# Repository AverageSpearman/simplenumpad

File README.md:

# simplenumpad
A very basic, hacked together mechanical numpad.

## Introduction

This was made with the goal of having a numpad to go with a mechanical keyboard lacking one.
Since I didn't want to bother with either buying a kit or going to a manufacturer to get a pcb, this is made using basically as few new parts as possible.
Most of the parts that aren't the electronics are just random garbage around the house.

## Parts List
Because this project doesn't use a PCB, all of the parts listed are through-hole components (THT).

|Part               |Quantity |
|:--:               |:--------|
|Cherry MX Switches | 17      |
|1n4148 Diode       | 17      |
|Arduino Pro Micro  | 1       |

That's pretty much it. You can even skip the diodes if you want to put in the anti-ghosting features in software. Stabilizers for the larger keys are optional.

## Layout
The layout is done in KiCad, but only because it's easy to get footprints for different kinds of mechanical switches, and print the design.
**The PCB design is used mainly as a wiring and layout guide. It is not meant to be manufactured and is not made to manufacturing specifications or common practice.**

## Assembly

### Circuit Board

The first step is to punch, drill, or otherwise make the holes to mount the switches. You'll want to use PCB mount switches if you can, but I got away with plate-mounted switches, since they still at least have that big peg in the middle. These switches will more or less **be stuck where they are after the build, for the most part.** This *is* a really hacky, dirty way of doing it, but it is cheap. Jam the switches in, and then use hot glue or some other adhesive should you need it. You can put your keycaps on as well, if you want.

### Wiring

Use the schematic and layout as a guide when wiring the rows and columns. Make sure all of your diodes are facing the same direction (If you get them all backwards you should be able to fix it in software, but only if they're all backwards).

## Code

This uses the SET library by RobTillaart ([Link](https://github.com/RobTillaart/SET)).
The code energizes columns and reads rows in a matrix, then puts them in sets and gets the difference to figure out which keys are newly pressed or released. The code will only press and release the keys as needed.

## Finished!

That's about it. Good luck!

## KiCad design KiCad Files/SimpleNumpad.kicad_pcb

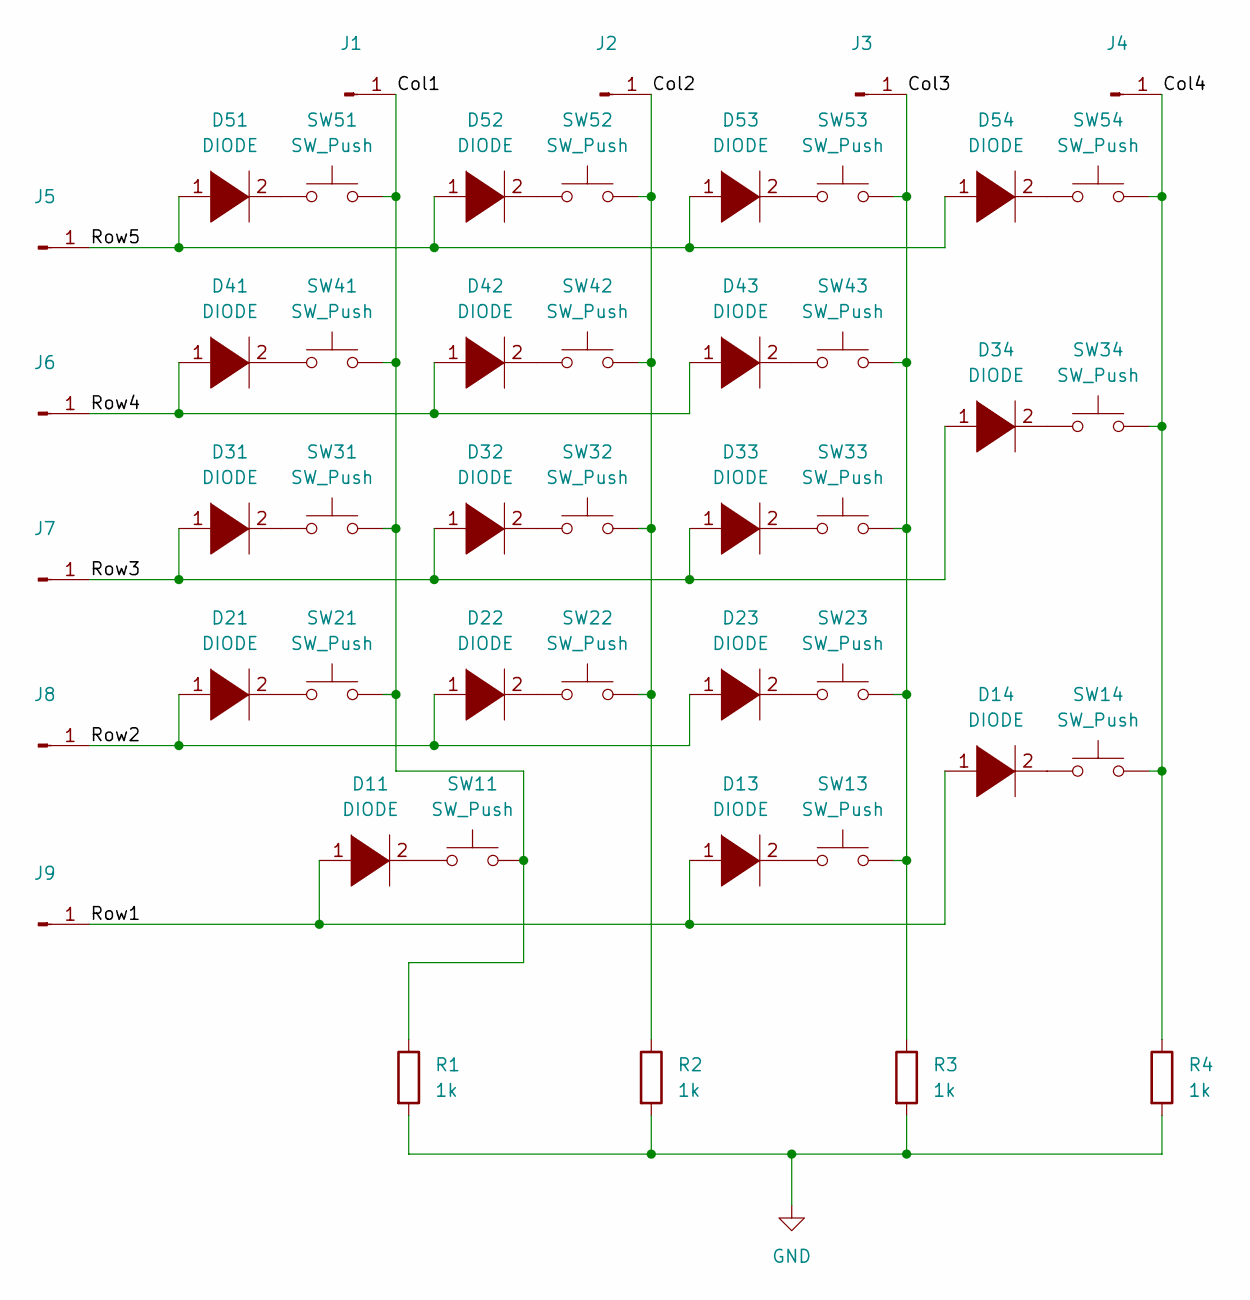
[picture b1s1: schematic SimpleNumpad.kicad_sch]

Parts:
D11, D13, D14, D21, D22, D23, D31, D32, D33, D34, D41, D42, D43, D51, D52, D53, D54: DIODE; D_DO-35_SOD27_P7.62mm_Horizontal
J1, J2, J3, J4, J5, J6, J7, J8, J9: (no value)
R1, R2, R3, R4: 1k; R_Axial_DIN0207_L6.3mm_D2.5mm_P10.16mm_Horizontal
SW11: SW_Push; SW_Cherry_MX_2.00u_PCB
SW13, SW21, SW22, SW23, SW31, SW32, SW33, SW41, SW42, SW43, SW51, SW52, SW53, SW54: SW_Push; SW_Cherry_MX_1.00u_PCB
SW14, SW34: SW_Push; SW_Cherry_MX_2.00u_Vertical_PCB

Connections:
/Col1: J1.1, R1.1, SW11.1, SW21.1, SW31.1, SW41.1, SW51.1
/Col2: J2.1, R2.1, SW22.1, SW32.1, SW42.1, SW52.1
/Col3: J3.1, R3.1, SW13.1, SW23.1, SW33.1, SW43.1, SW53.1
/Col4: J4.1, R4.1, SW14.1, SW34.1, SW54.1
/Row1: D11.1 (K), D13.1 (K), D14.1 (K), J9.1
/Row2: D21.1 (K), D22.1 (K), D23.1 (K), J8.1
/Row3: D31.1 (K), D32.1 (K), D33.1 (K), D34.1 (K), J7.1
/Row4: D41.1 (K), D42.1 (K), D43.1 (K), J6.1
/Row5: D51.1 (K), D52.1 (K), D53.1 (K), D54.1 (K), J5.1
GND: R1.2, R2.2, R3.2, R4.2
unnamed: D11.2 (A), SW11.2
unnamed: D13.2 (A), SW13.2
unnamed: D14.2 (A), SW14.2
unnamed: D21.2 (A), SW21.2
unnamed: D22.2 (A), SW22.2
unnamed: D23.2 (A), SW23.2
unnamed: D31.2 (A), SW31.2
unnamed: D32.2 (A), SW32.2
unnamed: D33.2 (A), SW33.2
unnamed: D34.2 (A), SW34.2
unnamed: D41.2 (A), SW41.2
unnamed: D42.2 (A), SW42.2
unnamed: D43.2 (A), SW43.2
unnamed: D51.2 (A), SW51.2
unnamed: D52.2 (A), SW52.2
unnamed: D53.2 (A), SW53.2
unnamed: D54.2 (A), SW54.2

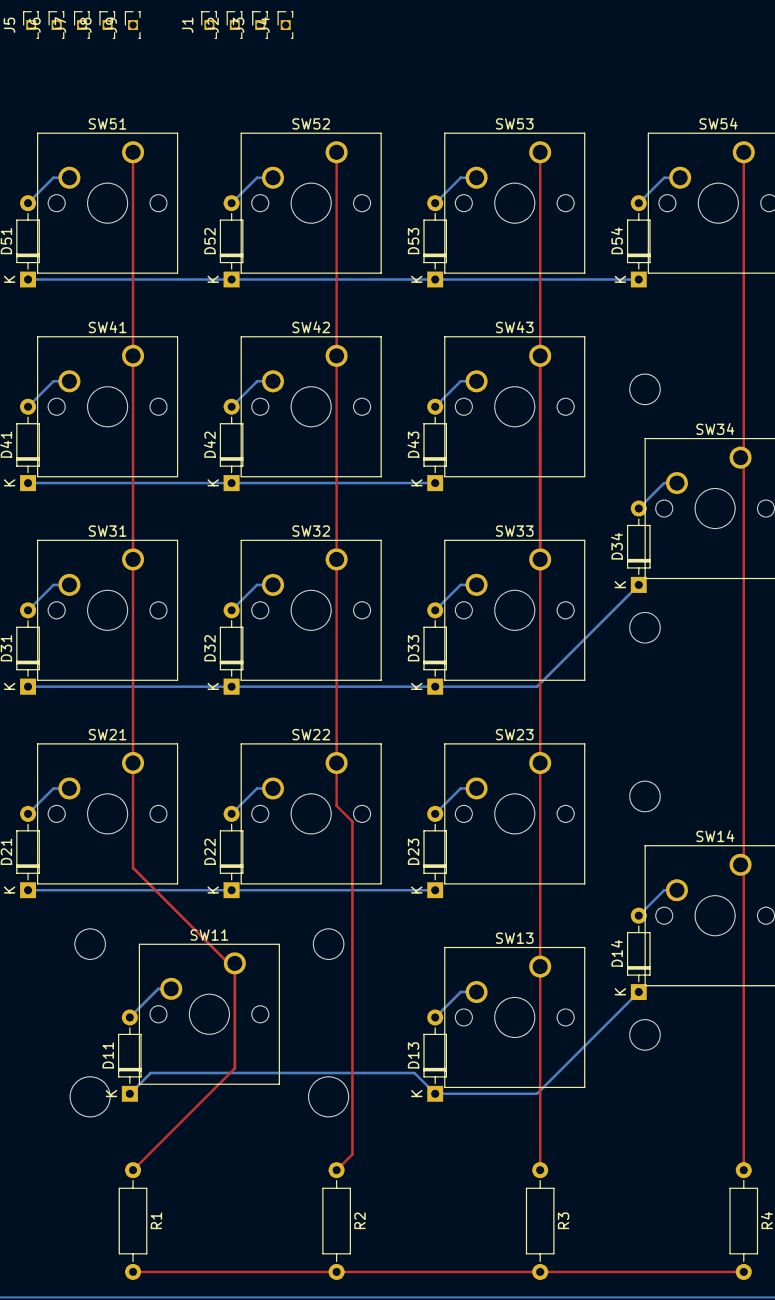
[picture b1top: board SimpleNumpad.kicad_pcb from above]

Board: 2 copper layers, 47 parts (0 on the bottom side), 27 nets.

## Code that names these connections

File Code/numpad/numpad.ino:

#include <set.h>

#include <Keyboard.h>
int row1 = 9;
int row2 = 8;
int row3 = 7;
int row4 = 6;
int row5 = 5;

int col1 = 15;
int col2 = 14;
int col3 = 16;
int col4 = 10;

int keypadPins[9] = {row1,row2,row3,row4,row5,col1,col2,col3,col4};
int keypadStatus[20];
int lastKeypadStatus[20];
Set keyPresses;
Set lastKeyPresses;

int waitRepeatCount = 10;
int curWaitCount = 0;
//char keyMatrix[20] = {'0', ',', '.', '\n',
//                      '1', '2', '3', ',',
//                      '4', '5', '6', ',',
//                      '7', '8', '9', '+',
//                      'L', '/', '*', '-'};

int keyMatrix[20] = {234, ',', 235, 224,
                      225, 226, 227, ',',
                      228, 229, 230, ',',
                      231, 232, 233, 223,
                      219, 220, 221, 222};
//Matrix
//[LCK  /   *   - ]
//[ 7   8   9   + ]
//[ 3   5   6   N ]
//[ 1   2   3   N ]
//[ 0   N   .  ENT]

//Val
//[LCK  /   *   - ]
//[ 7   8   9   + ]
//[ 3   5   6   N ]
//[ 1   2   3   N ]
//[ 0   N   .  ENT]

//220 '\334' Keypad / 
//221 '\335' Keypad * 
//222 '\336' Keypad - 
//223 '\337' Keypad + 
//224 '\340' Keypad ENTER 
//225 '\341' Keypad 1 and End 
//226 '\342' Keypad 2 and Down Arrow 
//227 '\343' Keypad 3 and PageDn 
//228 '\344' Keypad 4 and Left Arrow 
//229 '\345' Keypad 5 
//230 '\346' Keypad 6 and Right Arrow 
//231 '\347' Keypad 7 and Home 
//232 '\350' Keypad 8 and Up Arrow 
//233 '\351' Keypad 9 and PageUp 
//234 '\352' Keypad 0 and Insert /235 '\353' Keypad . and Delete
//219 Keypad Numlock
void setup() {
  Serial.begin(9600);
  // put your setup code here, to run once:
  for (int i=0; i<9; i++)
  {
    pinMode(keypadPins[i], INPUT);
    digitalWrite(keypadPins[i], LOW);
  }
}

void loop() {
  // put your main code here, to run repeatedly:
  getKeypadStatus();
  
  if(!array_cmp(keypadStatus, lastKeypadStatus, 20, 20)){
    curWaitCount = 0;
    //Keyboard.releaseAll();
    Serial.print("Keys changed:");
    keyPresses.clear();
    for(int i = 0; i < 20; i++){
      if(keypadStatus[i] < 1) break;
      keyPresses.add(keypadStatus[i]-1);
      Serial.print(keyMatrix[keypadStatus[i]-1]);
    }
    Set released = (lastKeyPresses - keyPresses);
    Set pressed = (keyPresses - lastKeyPresses );
    if(!pressed.isEmpty()) Keyboard.press(keyMatrix[pressed.first()]);
    if(!released.isEmpty()) Keyboard.release(keyMatrix[released.first()]);
    Serial.print(" ");
    Serial.print(released.count());
    Serial.print(" Released ");
    Serial.print(pressed.count());
    Serial.print(" Pressed ");
    
    Serial.print("\n");
    
  }
  
  
  array_copy(keypadStatus, lastKeypadStatus, 20, 20);  
  lastKeyPresses.clear();
  for(int i = 0; i < 20; i++){
    if(lastKeypadStatus[i] < 1) break;
    lastKeyPresses.add(lastKeypadStatus[i]-1);
  }
}

void getKeypadStatus()
{
  int rowPins[5] = {row1, row2, row3, row4, row5};  // row pins are 2, 7, 6, and 1 of the keypad
  int columnPins[4] = {col1, col2, col3, col4};  // column pins are pins 2, 4, and 5 of the keypad
  memset(keypadStatus, 0, sizeof(keypadStatus));
  int keypadIndex = 0;
  /* initialize all pins, inputs w/ pull-ups */
  for (int i=0; i<9; i++)
  {
    pinMode(keypadPins[i], INPUT);
    digitalWrite(keypadPins[i], HIGH);
  }
  
  for (int col=0; col<4; col++)
  {  // initial for loop to check all 4 cols
    pinMode(columnPins[col], OUTPUT);  // set the row pin as an output
    digitalWrite(columnPins[col], LOW);  // pull the row pins low
    for (int row=0; row<5; row++)
    {  // embedded for loop to check all 5 rows of each column
      if (!digitalRead(rowPins[row]))
      {
        int bitPos = ((row+1)*4 + (col+1) - 5)+1;
        //keypadStatus |= 1 << ((row+1)*4 + (col+1) - 5);  // set the status bit of the keypad return value
        keypadStatus[keypadIndex] = bitPos;  // set the status bit of the keypad return value
        keypadIndex++;
        if(keypadIndex == 20) keypadIndex = 0;
      }
    }
    pinMode(columnPins[col], INPUT);  // reset the row pin as an input
    digitalWrite(columnPins[col], HIGH);  // pull the row pin high
  }
}
void array_copy(int* a, int* b, int len_a, int len_b){
  int n;
  for(n = 0; n < len_a; n++) b[n] = a[n];
}
boolean array_cmp(int *a, int *b, int len_a, int len_b){
      int n;

      // if their lengths are different, return false
      if (len_a != len_b) return false;

      // test each element to be the same. if not, return false
      for (n=0;n<len_a;n++) if (a[n]!=b[n]) return false;

      //ok, if we have not returned yet, they are equal :)
      return true;
}
